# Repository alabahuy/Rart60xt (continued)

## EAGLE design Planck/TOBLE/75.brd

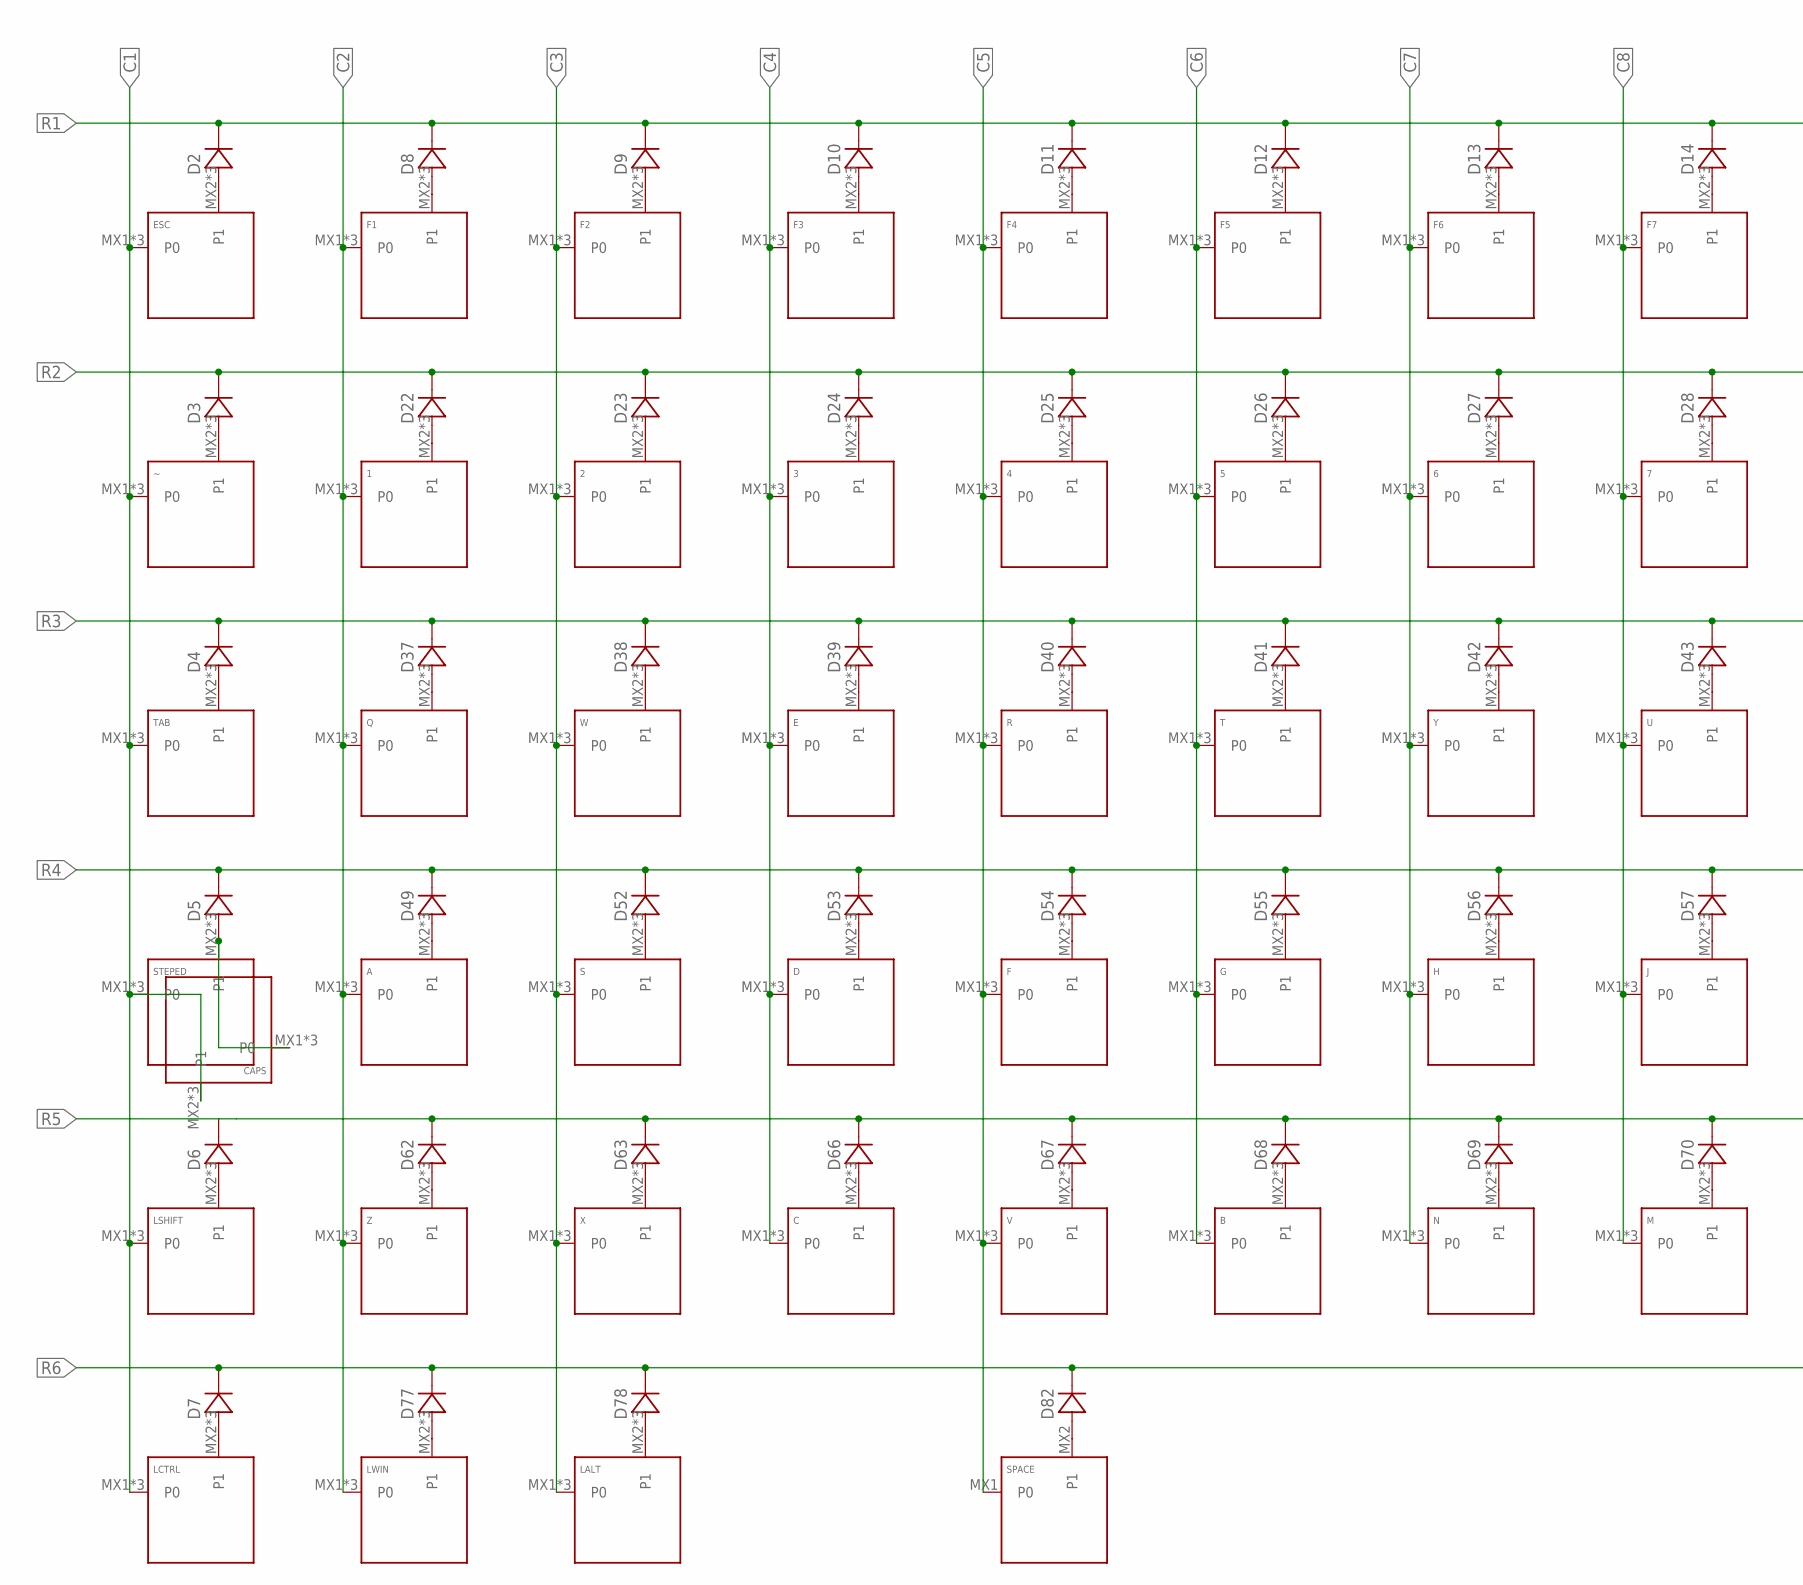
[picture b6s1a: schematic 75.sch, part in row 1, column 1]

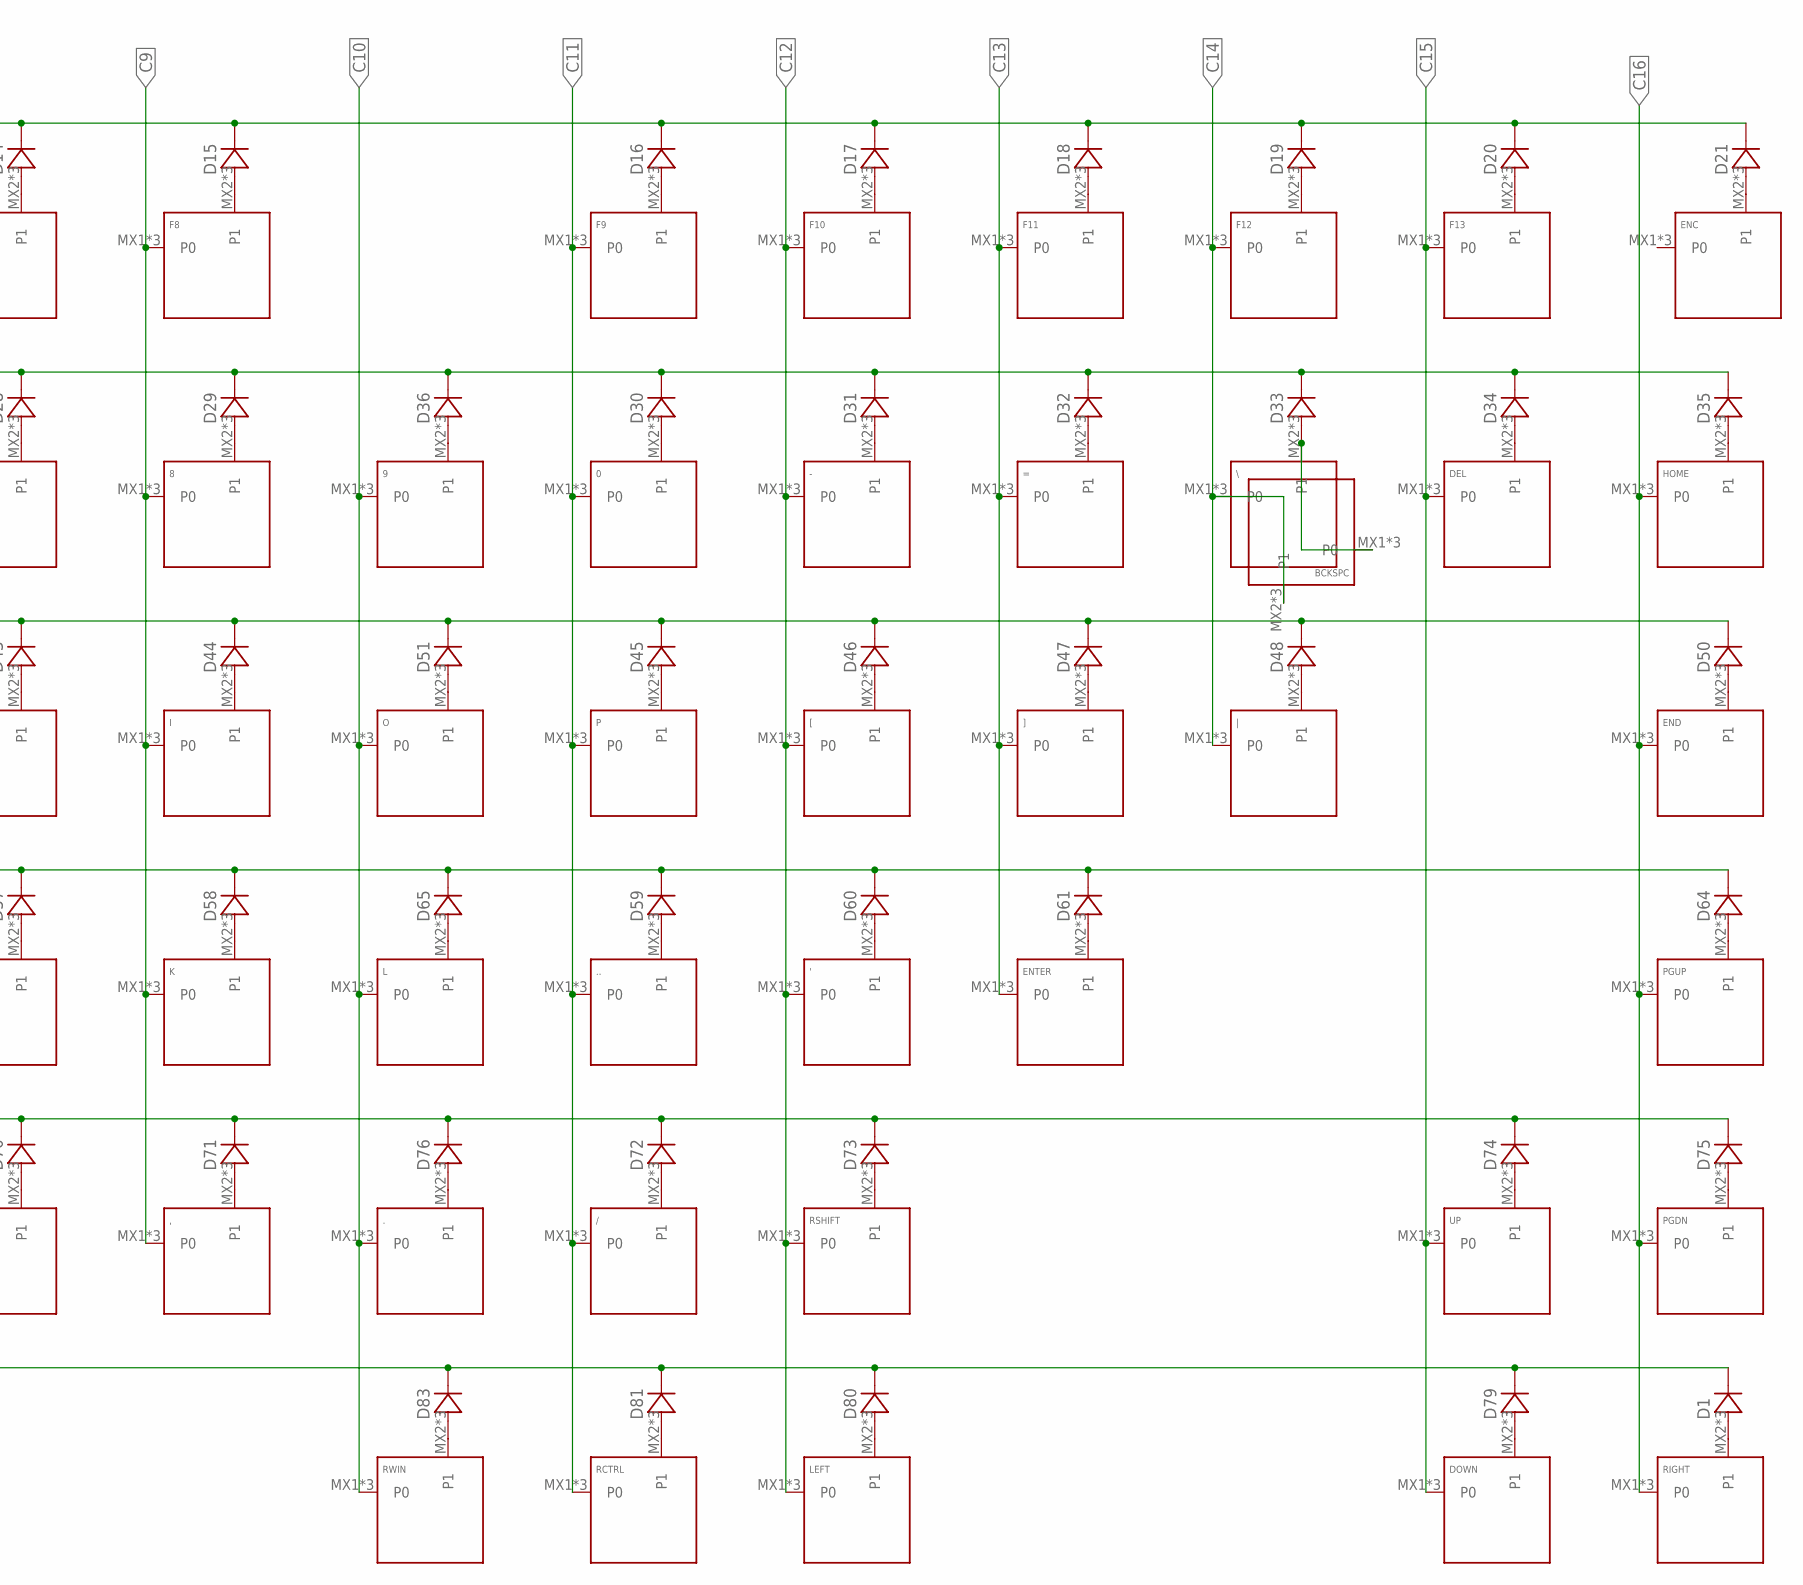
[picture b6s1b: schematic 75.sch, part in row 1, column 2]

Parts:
0, 1, 2, 3, 4, 5, 6, 7, 8, 9, ., ..: KEYSWITCH-PLAIN-MXHSPCB-1U; MXHSPCB-1U
': KEYSWITCH-PLAIN-MXHSPCB-1U; MXHSPCB-1U
,: KEYSWITCH-PLAIN-MXHSPCB-1U; MXHSPCB-1U
-: KEYSWITCH-PLAIN-MXHSPCB-1U; MXHSPCB-1U
/: KEYSWITCH-PLAIN-MXHSPCB-1U; MXHSPCB-1U
=: KEYSWITCH-PLAIN-MXHSPCB-1U; MXHSPCB-1U
A: KEYSWITCH-PLAIN-MXHSPCB-1U; MXHSPCB-1U
B: KEYSWITCH-PLAIN-MXHSPCB-1U; MXHSPCB-1U
BCKSPC: KEYSWITCH-PLAIN-MXHSPCB-2U; MXHSPCB-2U
C: KEYSWITCH-PLAIN-MXHSPCB-1U; MXHSPCB-1U
CAPS: KEYSWITCH-PLAIN-MXHSPCB-1U; MXHSPCB-1U
D: KEYSWITCH-PLAIN-MXHSPCB-1U; MXHSPCB-1U
D1, D2, D3, D4, D5, D6, D7, D8, D9, D10, D11, D12, D13, D14, D15, D16, D17, D18, D19, D20, D21, D22, D23, D24, D25, D26, D27, D28, D29, D30, D31, D32, D33, D34, D35, D36, D37, D38, D39, D40, D41, D42, D43, D44, D45, D46, D47, D48, D49, D50, D51, D52, D53, D54, D55, D56, D57, D58, D59, D60, D61, D62, D63, D64, D65, D66, D67, D68, D69, D70, D71, D72, D73, D74, D75, D76, D77, D78, D79, D80, D81, D82, D83: DIODE-SOD-123; SOD-123
DEL: KEYSWITCH-PLAIN-MXHSPCB-1U; MXHSPCB-1U
DOWN: KEYSWITCH-PLAIN-MXHSPCB-1U; MXHSPCB-1U
E: KEYSWITCH-PLAIN-MXHSPCB-1U; MXHSPCB-1U
ENC: KEYSWITCH-PLAIN-MXHSPCB-1U; MXHSPCB-1U
END: KEYSWITCH-PLAIN-MXHSPCB-1U; MXHSPCB-1U
ENTER: KEYSWITCH-PLAIN-MXHSPCB-2U-FLIPPED; MXHSPCB-2U-FLIPPED
ESC: KEYSWITCH-PLAIN-MXHSPCB-1U; MXHSPCB-1U
F, F1, F2, F3, F4, F5, F6, F7, F8, F9, F10, F11, F12, F13: KEYSWITCH-PLAIN-MXHSPCB-1U; MXHSPCB-1U
G: KEYSWITCH-PLAIN-MXHSPCB-1U; MXHSPCB-1U
H: KEYSWITCH-PLAIN-MXHSPCB-1U; MXHSPCB-1U
HOME: KEYSWITCH-PLAIN-MXHSPCB-1U; MXHSPCB-1U
I: KEYSWITCH-PLAIN-MXHSPCB-1U; MXHSPCB-1U
J: KEYSWITCH-PLAIN-MXHSPCB-1U; MXHSPCB-1U
K: KEYSWITCH-PLAIN-MXHSPCB-1U; MXHSPCB-1U
L: KEYSWITCH-PLAIN-MXHSPCB-1U; MXHSPCB-1U
LALT: KEYSWITCH-PLAIN-MXHSPCB-1U; MXHSPCB-1U
LCTRL: KEYSWITCH-PLAIN-MXHSPCB-1U; MXHSPCB-1U
LEFT: KEYSWITCH-PLAIN-MXHSPCB-1U; MXHSPCB-1U
LSHIFT: KEYSWITCH-PLAIN-MXHS-2U; MXHS-2U
LWIN: KEYSWITCH-PLAIN-MXHSPCB-1U; MXHSPCB-1U
M: KEYSWITCH-PLAIN-MXHSPCB-1U; MXHSPCB-1U
N: KEYSWITCH-PLAIN-MXHSPCB-1U; MXHSPCB-1U
O: KEYSWITCH-PLAIN-MXHSPCB-1U; MXHSPCB-1U
P: KEYSWITCH-PLAIN-MXHSPCB-1U; MXHSPCB-1U
PGDN: KEYSWITCH-PLAIN-MXHSPCB-1U; MXHSPCB-1U
PGUP: KEYSWITCH-PLAIN-MXHSPCB-1U; MXHSPCB-1U
Q: KEYSWITCH-PLAIN-MXHSPCB-1U; MXHSPCB-1U
R: KEYSWITCH-PLAIN-MXHSPCB-1U; MXHSPCB-1U
RCTRL: KEYSWITCH-PLAIN-MXHSPCB-1U; MXHSPCB-1U
RIGHT: KEYSWITCH-PLAIN-MXHSPCB-1U; MXHSPCB-1U
RSHIFT: KEYSWITCH-PLAIN-MXHSPCB-1U; MXHSPCB-1U
RWIN: KEYSWITCH-PLAIN-MXHSPCB-1U; MXHSPCB-1U
S: KEYSWITCH-PLAIN-MXHSPCB-1U; MXHSPCB-1U
SPACE: KEYSWITCH-PLAIN-MXHSPCB-6.25U-FLIPPED; MXHSPCB-6.25U-FLIPPED
STEPED: KEYSWITCH-PLAIN-MXHSPCB-1U; MXHSPCB-1U
T: KEYSWITCH-PLAIN-MXHSPCB-1U; MXHSPCB-1U
TAB: KEYSWITCH-PLAIN-MXHSPCB-1U; MXHSPCB-1U
U: KEYSWITCH-PLAIN-MXHSPCB-1U; MXHSPCB-1U
UP: KEYSWITCH-PLAIN-MXHSPCB-1U; MXHSPCB-1U
V: KEYSWITCH-PLAIN-MXHSPCB-1U; MXHSPCB-1U
W: KEYSWITCH-PLAIN-MXHSPCB-1U; MXHSPCB-1U
X: KEYSWITCH-PLAIN-MXHSPCB-1U; MXHSPCB-1U
Y: KEYSWITCH-PLAIN-MXHSPCB-1U; MXHSPCB-1U
Z: KEYSWITCH-PLAIN-MXHSPCB-1U; MXHSPCB-1U
[: KEYSWITCH-PLAIN-MXHSPCB-1U; MXHSPCB-1U
\\: KEYSWITCH-PLAIN-MXHSPCB-1U; MXHSPCB-1U
]: KEYSWITCH-PLAIN-MXHSPCB-1U; MXHSPCB-1U
|: KEYSWITCH-PLAIN-MXHSPCB-1U; MXHSPCB-1U
~: KEYSWITCH-PLAIN-MXHSPCB-1U; MXHSPCB-1U

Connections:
C1: CAPS.MX2 (P1), CAPS.P$3 (P1), CAPS.P$4 (P1), ESC.MX1 (P0), ESC.P$1 (P0), ESC.P$2 (P0), LCTRL.MX1 (P0), LCTRL.P$1 (P0), LCTRL.P$2 (P0), LSHIFT.MX1 (P0), LSHIFT.P$3 (P0), LSHIFT.P$4 (P0), STEPED.MX1 (P0), STEPED.P$1 (P0), STEPED.P$2 (P0), TAB.MX1 (P0), TAB.P$1 (P0), TAB.P$2 (P0), ~.MX1 (P0), ~.P$1 (P0), ~.P$2 (P0)
C2: 1.MX1 (P0), 1.P$1 (P0), 1.P$2 (P0), A.MX1 (P0), A.P$1 (P0), A.P$2 (P0), F1.MX1 (P0), F1.P$1 (P0), F1.P$2 (P0), LWIN.MX1 (P0), LWIN.P$1 (P0), LWIN.P$2 (P0), Q.MX1 (P0), Q.P$1 (P0), Q.P$2 (P0), Z.MX1 (P0), Z.P$1 (P0), Z.P$2 (P0)
C3: 2.MX1 (P0), 2.P$1 (P0), 2.P$2 (P0), F2.MX1 (P0), F2.P$1 (P0), F2.P$2 (P0), LALT.MX1 (P0), LALT.P$1 (P0), LALT.P$2 (P0), S.MX1 (P0), S.P$1 (P0), S.P$2 (P0), W.MX1 (P0), W.P$1 (P0), W.P$2 (P0), X.MX1 (P0), X.P$1 (P0), X.P$2 (P0)
C4: 3.MX1 (P0), 3.P$1 (P0), 3.P$2 (P0), C.MX1 (P0), C.P$1 (P0), C.P$2 (P0), D.MX1 (P0), D.P$1 (P0), D.P$2 (P0), E.MX1 (P0), E.P$1 (P0), E.P$2 (P0), F3.MX1 (P0), F3.P$1 (P0), F3.P$2 (P0)
C5: 4.MX1 (P0), 4.P$1 (P0), 4.P$2 (P0), F.MX1 (P0), F.P$1 (P0), F.P$2 (P0), F4.MX1 (P0), F4.P$1 (P0), F4.P$2 (P0), R.MX1 (P0), R.P$1 (P0), R.P$2 (P0), SPACE.MX1 (P0), V.MX1 (P0), V.P$1 (P0), V.P$2 (P0)
C6: 5.MX1 (P0), 5.P$1 (P0), 5.P$2 (P0), B.MX1 (P0), B.P$1 (P0), B.P$2 (P0), F5.MX1 (P0), F5.P$1 (P0), F5.P$2 (P0), G.MX1 (P0), G.P$1 (P0), G.P$2 (P0), T.MX1 (P0), T.P$1 (P0), T.P$2 (P0)
C7: 6.MX1 (P0), 6.P$1 (P0), 6.P$2 (P0), F6.MX1 (P0), F6.P$1 (P0), F6.P$2 (P0), H.MX1 (P0), H.P$1 (P0), H.P$2 (P0), N.MX1 (P0), N.P$1 (P0), N.P$2 (P0), Y.MX1 (P0), Y.P$1 (P0), Y.P$2 (P0)
C8: 7.MX1 (P0), 7.P$1 (P0), 7.P$2 (P0), F7.MX1 (P0), F7.P$1 (P0), F7.P$2 (P0), J.MX1 (P0), J.P$1 (P0), J.P$2 (P0), M.MX1 (P0), M.P$1 (P0), M.P$2 (P0), U.MX1 (P0), U.P$1 (P0), U.P$2 (P0)
C9: 8.MX1 (P0), 8.P$1 (P0), 8.P$2 (P0), ,.MX1 (P0), ,.P$1 (P0), ,.P$2 (P0), F8.MX1 (P0), F8.P$1 (P0), F8.P$2 (P0), I.MX1 (P0), I.P$1 (P0), I.P$2 (P0), K.MX1 (P0), K.P$1 (P0), K.P$2 (P0)
C10: 9.MX1 (P0), 9.P$1 (P0), 9.P$2 (P0), ..MX1 (P0), ..P$1 (P0), ..P$2 (P0), L.MX1 (P0), L.P$1 (P0), L.P$2 (P0), O.MX1 (P0), O.P$1 (P0), O.P$2 (P0), RWIN.MX1 (P0), RWIN.P$1 (P0), RWIN.P$2 (P0)
C11: 0.MX1 (P0), 0.P$1 (P0), 0.P$2 (P0), ...MX1 (P0), ...P$1 (P0), ...P$2 (P0), /.MX1 (P0), /.P$1 (P0), /.P$2 (P0), F9.MX1 (P0), F9.P$1 (P0), F9.P$2 (P0), P.MX1 (P0), P.P$1 (P0), P.P$2 (P0), RCTRL.MX1 (P0), RCTRL.P$1 (P0), RCTRL.P$2 (P0)
C12: '.MX1 (P0), '.P$1 (P0), '.P$2 (P0), -.MX1 (P0), -.P$1 (P0), -.P$2 (P0), F10.MX1 (P0), F10.P$1 (P0), F10.P$2 (P0), LEFT.MX1 (P0), LEFT.P$1 (P0), LEFT.P$2 (P0), RSHIFT.MX1 (P0), RSHIFT.P$1 (P0), RSHIFT.P$2 (P0), [.MX1 (P0), [.P$1 (P0), [.P$2 (P0)
C13: =.MX1 (P0), =.P$1 (P0), =.P$2 (P0), ENTER.MX1 (P0), ENTER.P$1 (P0), ENTER.P$2 (P0), F11.MX1 (P0), F11.P$1 (P0), F11.P$2 (P0), ].MX1 (P0), ].P$1 (P0), ].P$2 (P0)
C14: BCKSPC.MX2 (P1), BCKSPC.P$3 (P1), BCKSPC.P$4 (P1), F12.MX1 (P0), F12.P$1 (P0), F12.P$2 (P0), \\.MX1 (P0), \\.P$1 (P0), \\.P$2 (P0), |.MX1 (P0), |.P$1 (P0), |.P$2 (P0)
C15: DEL.MX1 (P0), DEL.P$1 (P0), DEL.P$2 (P0), DOWN.MX1 (P0), DOWN.P$1 (P0), DOWN.P$2 (P0), F13.MX1 (P0), F13.P$1 (P0), F13.P$2 (P0), UP.MX1 (P0), UP.P$1 (P0), UP.P$2 (P0)
C16: END.MX1 (P0), END.P$1 (P0), END.P$2 (P0), HOME.MX1 (P0), HOME.P$1 (P0), HOME.P$2 (P0), PGDN.MX1 (P0), PGDN.P$1 (P0), PGDN.P$2 (P0), PGUP.MX1 (P0), PGUP.P$1 (P0), PGUP.P$2 (P0), RIGHT.MX1 (P0), RIGHT.P$1 (P0), RIGHT.P$2 (P0)
unnamed: D2.A, ESC.MX2 (P1), ESC.P$3 (P1), ESC.P$4 (P1)
unnamed: D3.A, ~.MX2 (P1), ~.P$3 (P1), ~.P$4 (P1)
unnamed: D4.A, TAB.MX2 (P1), TAB.P$3 (P1), TAB.P$4 (P1)
unnamed: CAPS.MX1 (P0), CAPS.P$1 (P0), CAPS.P$2 (P0), D5.A, STEPED.MX2 (P1), STEPED.P$3 (P1), STEPED.P$4 (P1)
unnamed: D6.A, LSHIFT.MX2 (P1), LSHIFT.P$1 (P1), LSHIFT.P$2 (P1)
unnamed: D7.A, LCTRL.MX2 (P1), LCTRL.P$3 (P1), LCTRL.P$4 (P1)
unnamed: D81.A, RCTRL.MX2 (P1), RCTRL.P$3 (P1), RCTRL.P$4 (P1)
unnamed: D8.A, F1.MX2 (P1), F1.P$3 (P1), F1.P$4 (P1)
unnamed: D9.A, F2.MX2 (P1), F2.P$3 (P1), F2.P$4 (P1)
unnamed: D10.A, F3.MX2 (P1), F3.P$3 (P1), F3.P$4 (P1)
unnamed: D11.A, F4.MX2 (P1), F4.P$3 (P1), F4.P$4 (P1)
unnamed: D12.A, F5.MX2 (P1), F5.P$3 (P1), F5.P$4 (P1)
unnamed: D13.A, F6.MX2 (P1), F6.P$3 (P1), F6.P$4 (P1)
unnamed: D14.A, F7.MX2 (P1), F7.P$3 (P1), F7.P$4 (P1)
unnamed: D15.A, F8.MX2 (P1), F8.P$3 (P1), F8.P$4 (P1)
unnamed: D16.A, F9.MX2 (P1), F9.P$3 (P1), F9.P$4 (P1)
unnamed: D17.A, F10.MX2 (P1), F10.P$3 (P1), F10.P$4 (P1)
unnamed: D18.A, F11.MX2 (P1), F11.P$3 (P1), F11.P$4 (P1)
unnamed: D19.A, F12.MX2 (P1), F12.P$3 (P1), F12.P$4 (P1)
unnamed: D20.A, F13.MX2 (P1), F13.P$3 (P1), F13.P$4 (P1)
unnamed: 1.MX2 (P1), 1.P$3 (P1), 1.P$4 (P1), D22.A
unnamed: 2.MX2 (P1), 2.P$3 (P1), 2.P$4 (P1), D23.A
unnamed: 3.MX2 (P1), 3.P$3 (P1), 3.P$4 (P1), D24.A
unnamed: 4.MX2 (P1), 4.P$3 (P1), 4.P$4 (P1), D25.A
unnamed: 5.MX2 (P1), 5.P$3 (P1), 5.P$4 (P1), D26.A
unnamed: 6.MX2 (P1), 6.P$3 (P1), 6.P$4 (P1), D27.A
unnamed: 7.MX2 (P1), 7.P$3 (P1), 7.P$4 (P1), D28.A
unnamed: 8.MX2 (P1), 8.P$3 (P1), 8.P$4 (P1), D29.A
unnamed: 0.MX2 (P1), 0.P$3 (P1), 0.P$4 (P1), D30.A
unnamed: -.MX2 (P1), -.P$3 (P1), -.P$4 (P1), D31.A
unnamed: =.MX2 (P1), =.P$3 (P1), =.P$4 (P1), D32.A
unnamed: BCKSPC.MX1 (P0), BCKSPC.P$1 (P0), BCKSPC.P$2 (P0), D33.A, \\.MX2 (P1), \\.P$3 (P1), \\.P$4 (P1)
unnamed: D34.A, DEL.MX2 (P1), DEL.P$3 (P1), DEL.P$4 (P1)
unnamed: D35.A, HOME.MX2 (P1), HOME.P$3 (P1), HOME.P$4 (P1)
unnamed: 9.MX2 (P1), 9.P$3 (P1), 9.P$4 (P1), D36.A
unnamed: D37.A, Q.MX2 (P1), Q.P$3 (P1), Q.P$4 (P1)
unnamed: D38.A, W.MX2 (P1), W.P$3 (P1), W.P$4 (P1)
unnamed: D39.A, E.MX2 (P1), E.P$3 (P1), E.P$4 (P1)
unnamed: D40.A, R.MX2 (P1), R.P$3 (P1), R.P$4 (P1)
unnamed: D41.A, T.MX2 (P1), T.P$3 (P1), T.P$4 (P1)
unnamed: D42.A, Y.MX2 (P1), Y.P$3 (P1), Y.P$4 (P1)
unnamed: D43.A, U.MX2 (P1), U.P$3 (P1), U.P$4 (P1)
unnamed: D21.A, ENC.MX2 (P1), ENC.P$3 (P1), ENC.P$4 (P1)
unnamed: D44.A, I.MX2 (P1), I.P$3 (P1), I.P$4 (P1)
unnamed: D51.A, O.MX2 (P1), O.P$3 (P1), O.P$4 (P1)
unnamed: D45.A, P.MX2 (P1), P.P$3 (P1), P.P$4 (P1)
unnamed: D46.A, [.MX2 (P1), [.P$3 (P1), [.P$4 (P1)
unnamed: D47.A, ].MX2 (P1), ].P$3 (P1), ].P$4 (P1)
unnamed: D48.A, |.MX2 (P1), |.P$3 (P1), |.P$4 (P1)
unnamed: D50.A, END.MX2 (P1), END.P$3 (P1), END.P$4 (P1)
unnamed: A.MX2 (P1), A.P$3 (P1), A.P$4 (P1), D49.A
unnamed: D52.A, S.MX2 (P1), S.P$3 (P1), S.P$4 (P1)
unnamed: D.MX2 (P1), D.P$3 (P1), D.P$4 (P1), D53.A
unnamed: D54.A, F.MX2 (P1), F.P$3 (P1), F.P$4 (P1)
unnamed: D55.A, G.MX2 (P1), G.P$3 (P1), G.P$4 (P1)
unnamed: D56.A, H.MX2 (P1), H.P$3 (P1), H.P$4 (P1)
unnamed: D57.A, J.MX2 (P1), J.P$3 (P1), J.P$4 (P1)
unnamed: D58.A, K.MX2 (P1), K.P$3 (P1), K.P$4 (P1)
unnamed: D65.A, L.MX2 (P1), L.P$3 (P1), L.P$4 (P1)
unnamed: ...MX2 (P1), ...P$3 (P1), ...P$4 (P1), D59.A
unnamed: '.MX2 (P1), '.P$3 (P1), '.P$4 (P1), D60.A
unnamed: D61.A, ENTER.MX2 (P1), ENTER.P$3 (P1), ENTER.P$4 (P1)
unnamed: D64.A, PGUP.MX2 (P1), PGUP.P$3 (P1), PGUP.P$4 (P1)
unnamed: D62.A, Z.MX2 (P1), Z.P$3 (P1), Z.P$4 (P1)
unnamed: D63.A, X.MX2 (P1), X.P$3 (P1), X.P$4 (P1)
unnamed: C.MX2 (P1), C.P$3 (P1), C.P$4 (P1), D66.A
unnamed: D67.A, V.MX2 (P1), V.P$3 (P1), V.P$4 (P1)
unnamed: B.MX2 (P1), B.P$3 (P1), B.P$4 (P1), D68.A
unnamed: D69.A, N.MX2 (P1), N.P$3 (P1), N.P$4 (P1)
unnamed: D70.A, M.MX2 (P1), M.P$3 (P1), M.P$4 (P1)
unnamed: ,.MX2 (P1), ,.P$3 (P1), ,.P$4 (P1), D71.A
unnamed: ..MX2 (P1), ..P$3 (P1), ..P$4 (P1), D76.A
unnamed: /.MX2 (P1), /.P$3 (P1), /.P$4 (P1), D72.A
unnamed: D73.A, RSHIFT.MX2 (P1), RSHIFT.P$3 (P1), RSHIFT.P$4 (P1)
unnamed: D75.A, PGDN.MX2 (P1), PGDN.P$3 (P1), PGDN.P$4 (P1)
unnamed: D74.A, UP.MX2 (P1), UP.P$3 (P1), UP.P$4 (P1)
unnamed: D77.A, LWIN.MX2 (P1), LWIN.P$3 (P1), LWIN.P$4 (P1)
unnamed: D78.A, LALT.MX2 (P1), LALT.P$3 (P1), LALT.P$4 (P1)
unnamed: D82.A, SPACE.MX2 (P1)
unnamed: D83.A, RWIN.MX2 (P1), RWIN.P$3 (P1), RWIN.P$4 (P1)
unnamed: D80.A, LEFT.MX2 (P1), LEFT.P$3 (P1), LEFT.P$4 (P1)
unnamed: D1.A, RIGHT.MX2 (P1), RIGHT.P$3 (P1), RIGHT.P$4 (P1)
unnamed: D79.A, DOWN.MX2 (P1), DOWN.P$3 (P1), DOWN.P$4 (P1)
R1: D2.C, D8.C, D9.C, D10.C, D11.C, D12.C, D13.C, D14.C, D15.C, D16.C, D17.C, D18.C, D19.C, D20.C, D21.C
R2: D3.C, D22.C, D23.C, D24.C, D25.C, D26.C, D27.C, D28.C, D29.C, D30.C, D31.C, D32.C, D33.C, D34.C, D35.C, D36.C
R3: D4.C, D37.C, D38.C, D39.C, D40.C, D41.C, D42.C, D43.C, D44.C, D45.C, D46.C, D47.C, D48.C, D50.C, D51.C
R4: D5.C, D49.C, D52.C, D53.C, D54.C, D55.C, D56.C, D57.C, D58.C, D59.C, D60.C, D61.C, D64.C, D65.C
R5: D6.C, D62.C, D63.C, D66.C, D67.C, D68.C, D69.C, D70.C, D71.C, D72.C, D73.C, D74.C, D75.C, D76.C
R6: D1.C, D7.C, D77.C, D78.C, D79.C, D80.C, D81.C, D82.C, D83.C

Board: 2 copper layers, 168 parts (168 on the bottom side), 105 nets, no tracks yet.

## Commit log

2022-08-16 add submodules
2022-08-16 Add Submodule
2022-08-16 resume
2022-08-16 Process
2022-08-16 break
2022-08-21 done
2022-09-07 add DB
2022-09-22 addadda
2022-11-01 addadd
2023-01-04 Update 75.b#1
